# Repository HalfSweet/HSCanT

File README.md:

# HSCanT

HSCanT 是一款USB转4路CAN FD工具，基于HPM5321芯片设计。

## 特性

- 支持4路CAN FD通道
- 每路CAN FD通道支持最高8Mbit/s的数据传输速率
- 支持上位机配置可选的120Ω终端电阻
- 每路通道均支持独立的TX、RX状态全彩LED指示
- 支持最高±58V的过压保护

## 致谢

感谢[RCSN](https://github.com/RCSN)大佬提供的思路，以及该项目的上下位机软件支持。

- 上位机：<https://github.com/RCSN/cangaroo_hpmicro_canfd_analyzer>
- 下位机：<https://github.com/RCSN/hpm_sdk_extra/tree/main/demos/cangaroo_hpmicro>

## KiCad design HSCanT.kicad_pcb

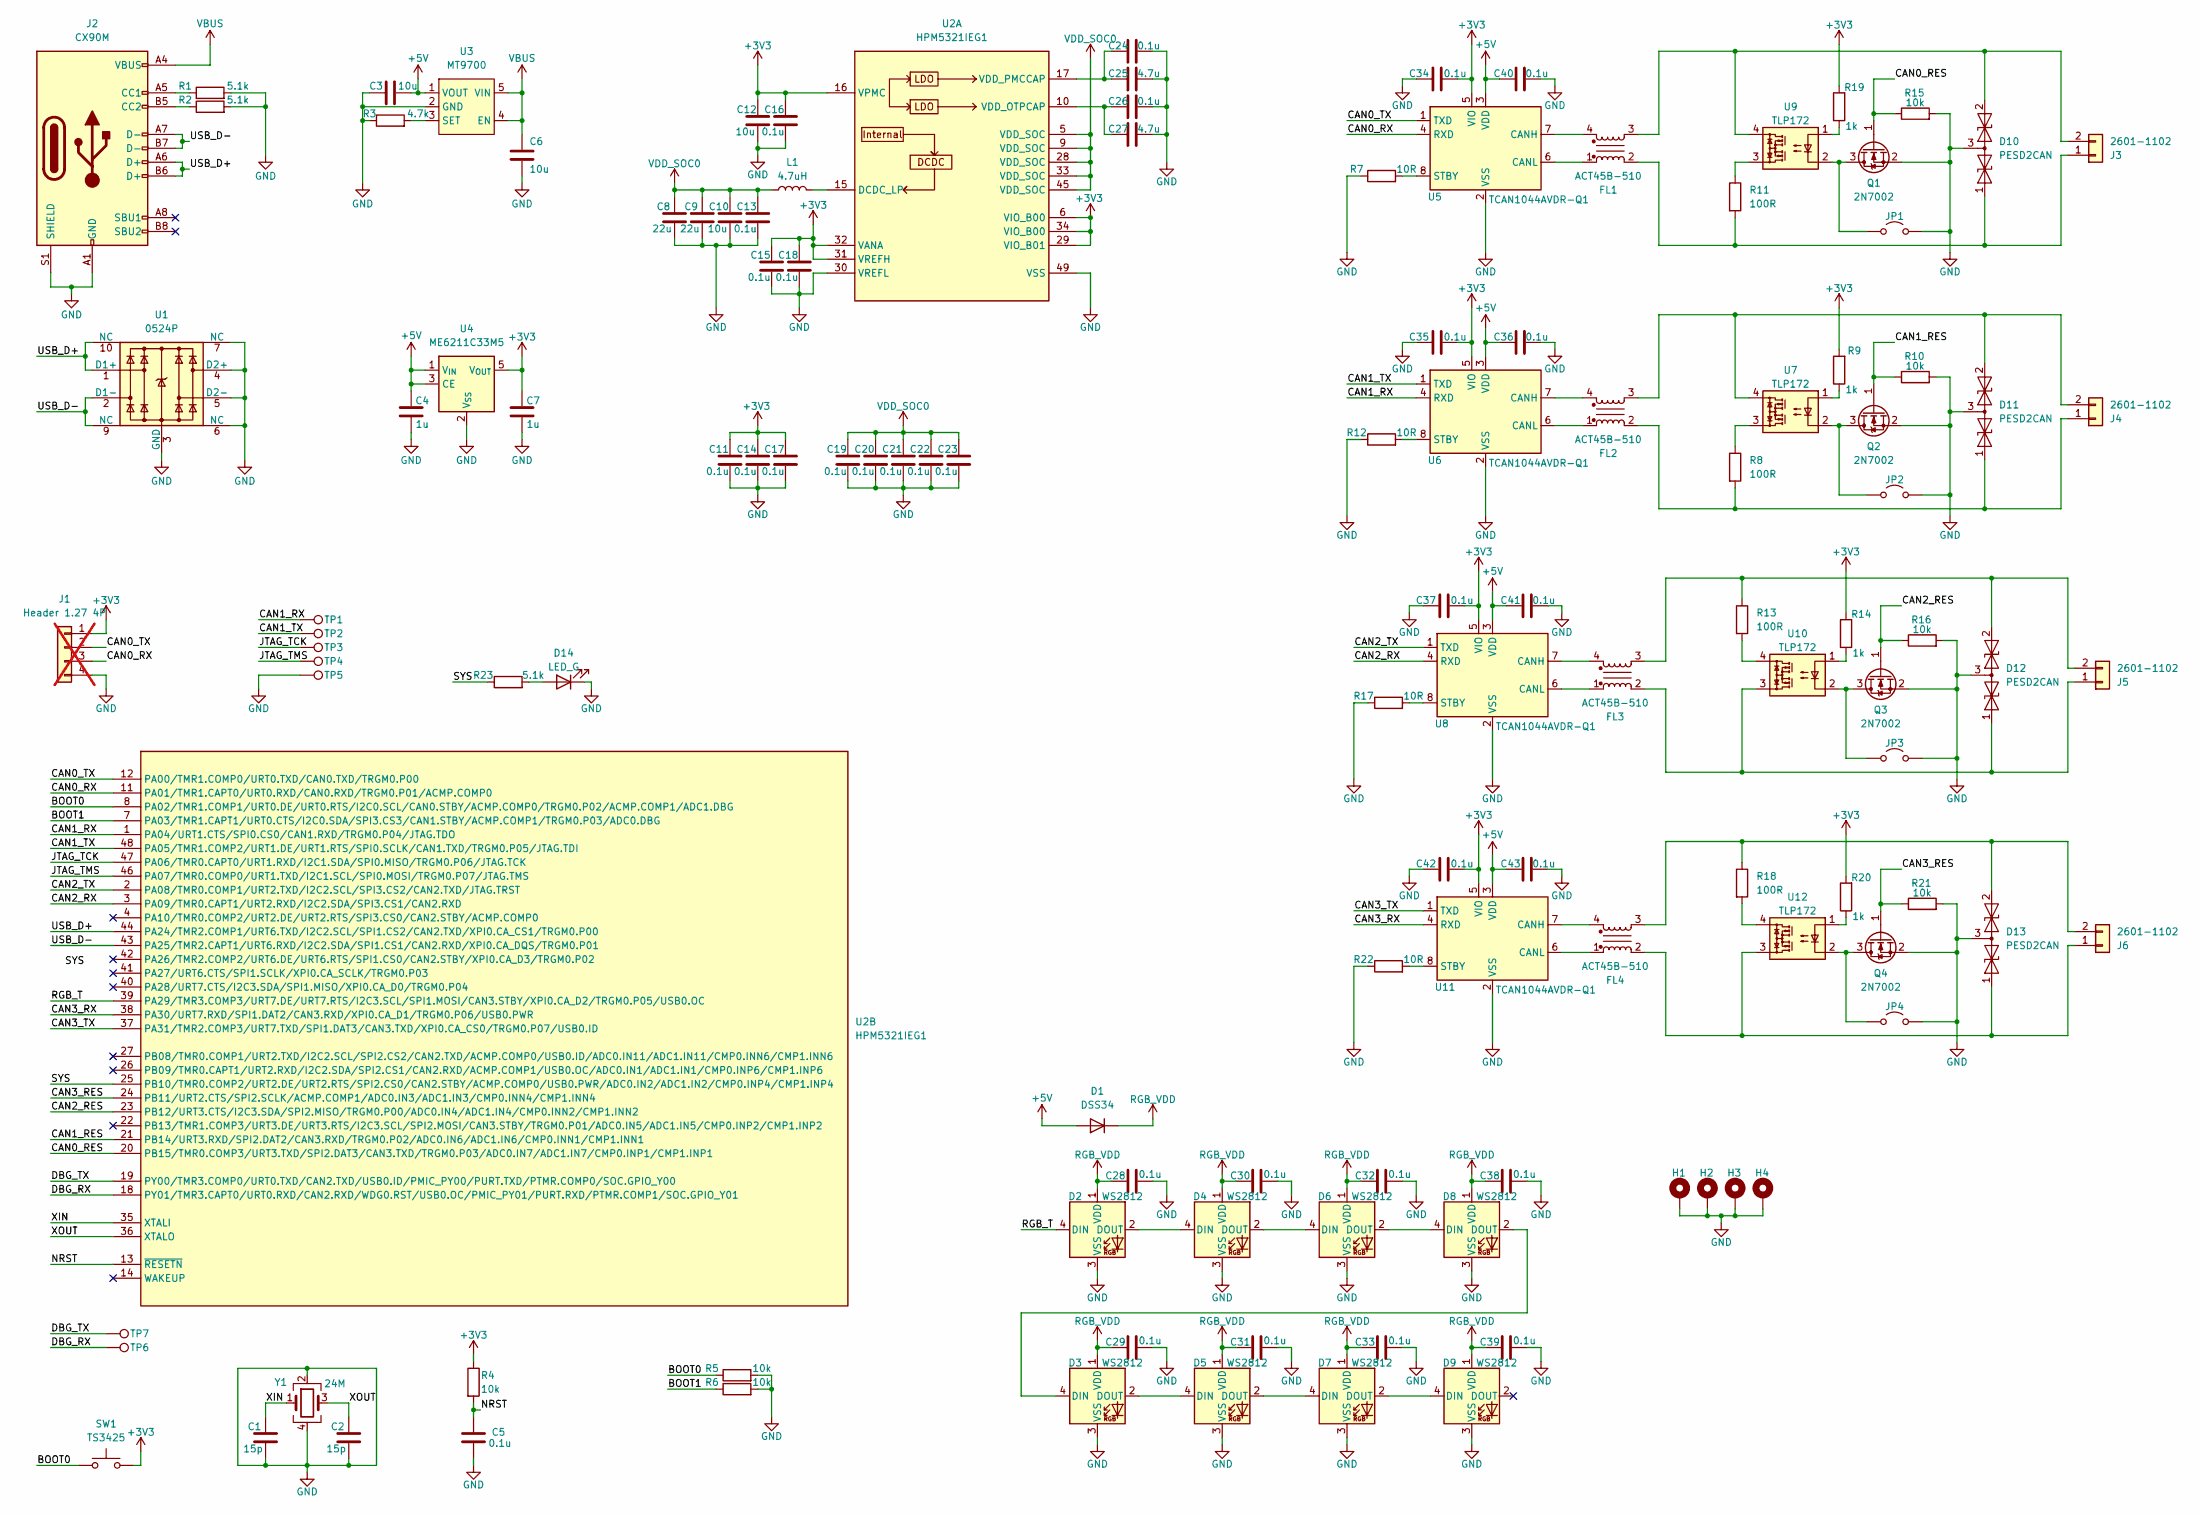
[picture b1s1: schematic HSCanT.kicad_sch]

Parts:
C1, C2: 15p; C_0402_1005Metric
C3, C6: 10u; C_0603_1608Metric
C4, C7: 1u; C_0402_1005Metric
C5, C11, C13, C14, C15, C16, C17, C18, C19, C20, C21, C22, C23, C24, C26, C28, C29, C30, C31, C32, C33, C34, C35, C36, C37, C38, C39, C40, C41, C42, C43: 0.1u; C_0402_1005Metric
C8, C9: 22u; C_0402_1005Metric
C10, C12: 10u; C_0402_1005Metric
C25, C27: 4.7u; C_0402_1005Metric
D1: DSS34; D_SOD-123
D2, D3, D4, D5, D6, D7, D8, D9: WS2812; LED_WS2812_0807
D10, D11, D12, D13: PESD2CAN; SOT-23
D14: LED_G; LED_0603_1608Metric
FL1, FL2, FL3, FL4: ACT45B-510; L_CommonModeChoke_Coilcraft_1812CAN
H1, H2, H3, H4: MountingHole_Pad; MountingHole_2.2mm_M2_Pad_TopBottom
J1: Header 1.27 4P; PinHeader_1x04_P1.27mm_Vertical; not fitted
J2: CX90M; USB-C-SMD_CX90M-16P
J3, J4, J5, J6: 2601-1102; WAGO-2601-1102
JP1, JP2, JP3, JP4: Jumper_2_Open; SolderJumper-2_P1.3mm_Open_RoundedPad1.0x1.5mm
L1: 4.7uH; L_1008_2520Metric
Q1, Q2, Q3, Q4: 2N7002; Diodes_DFN1006-3
R1, R2, R23: 5.1k; R_0402_1005Metric
R3: 4.7k; R_0402_1005Metric
R4, R5, R6, R10, R15, R16, R21: 10k; R_0402_1005Metric
R7, R12, R17, R22: 10R; R_0402_1005Metric
R8, R11, R13, R18: 100R; R_1206_3216Metric
R9, R14, R19, R20: 1k; R_0402_1005Metric
SW1: TS3425; SW_SPST_PTS810
TP1, TP2, TP3, TP4, TP5, TP6, TP7: TestPoint; TestPoint_Pad_D1.0mm
U1: 0524P; USON-10_2.5x1.0mm_P0.5mm
U2: HPM5321IEG1; QFN-48-1EP_6x6mm_P0.4mm_EP4.2x4.2mm
U3: MT9700; SOT-23-5
U4: ME6211C33M5; SOT-23-5
U5, U6, U8, U11: TCAN1044AVDR-Q1; DFN-8-1EP_3x3mm_P0.65mm_EP1.55x2.4mm
U7, U9, U10, U12: TLP172; SOP-4_3.8x4.1mm_P2.54mm
Y1: 24M; Crystal_SMD_2016-4Pin_2.0x1.6mm

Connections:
+3V3: C7.1, C11.1, C12.1, C14.1, C15.1, C16.1, C17.1, C18.1, C34.2, C35.2, C37.2, C42.2, J1.1, R4.1, R9.2, R14.2, R19.2, R20.2, SW1.2, U2.6 (VIO_B00), U2.16 (VPMC), U2.29 (VIO_B01), U2.31 (VREFH), U2.32 (VANA), U2.34 (VIO_B00), U4.5 (V_{OUT}), U5.5 (VIO), U6.5 (VIO), U8.5 (VIO), U11.5 (VIO)
+5V: C3.2, C4.1, C36.1, C40.1, C41.1, C43.1, D1.2 (A), U3.1 (VOUT), U4.1 (V_{IN}), U4.3 (CE), U5.3 (VDD), U6.3 (VDD), U8.3 (VDD), U11.3 (VDD)
/BOOT0: R5.1, SW1.1, U2.8 (PA02/TMR1.COMP1/URT0.DE/URT0.RTS/I2C0.S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)
/BOOT1: R6.1, U2.7 (PA03/TMR1.CAPT1/URT0.CTS/I2C0.SDA/SPI3.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)
/CAN0_RES: Q1.1 (G), R15.1, U2.20 (PB15/TMR0.COMP3/URT3.TXD/SPI2.DAT3/CAN3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)
/CAN0_RX: J1.3, U2.11 (PA01/TMR1.CAPT0/URT0.RXD/CAN0.RXD/TRGM0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), U5.4 (RXD)
/CAN0_TX: J1.2, U2.12 (PA00/TMR1.COMP0/URT0.TXD/CAN0.TXD/TRGM0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), U5.1 (TXD)
/CAN1_RES: Q2.1 (G), R10.1, U2.21 (PB14/URT3.RXD/SPI2.DAT2/CAN3.RXD/TRGM0.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)
/CAN1_RX: TP1.1, U2.1 (PA04/URT1.CTS/SPI0.CS0/CAN1.RXD/TRGM0.P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), U6.4 (RXD)
/CAN1_TX: TP2.1, U2.48 (PA05/TMR1.COMP2/URT1.DE/URT1.RTS/SPI0.S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), U6.1 (TXD)
/CAN2_RES: Q3.1 (G), R16.1, U2.23 (PB12/URT3.CTS/I2C3.SDA/SPI2.MISO/TRGM0.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)
/CAN2_RX: U2.3 (PA09/TMR0.CAPT1/URT2.RXD/I2C2.SDA/SPI3.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), U8.4 (RXD)
/CAN2_TX: U2.2 (PA08/TMR0.COMP1/URT2.TXD/I2C2.SCL/SPI3.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), U8.1 (TXD)
/CAN3_RES: Q4.1 (G), R21.1, U2.24 (PB11/URT2.CTS/SPI2.SCLK/ACMP.COMP1/ADC0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)
/CAN3_RX: U2.38 (PA30/URT7.RXD/SPI1.DAT2/CAN3.RXD/XPI0.C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), U11.4 (RXD)
/CAN3_TX: U2.37 (PA31/TMR2.COMP3/URT7.TXD/SPI1.DAT3/CAN3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), U11.1 (TXD)
/DBG_RX: TP6.1, U2.18 (PY01/TMR3.CAPT0/URT0.RXD/CAN2.RXD/WDG0.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)
/DBG_TX: TP7.1, U2.19 (PY00/TMR3.COMP0/URT0.TXD/CAN2.TXD/USB0.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)
/JTAG_TCK: TP3.1, U2.47 (PA06/TMR0.CAPT0/URT1.RXD/I2C1.SDA/SPI0.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)
/JTAG_TMS: TP4.1, U2.46 (PA07/TMR0.COMP0/URT1.TXD/I2C1.SCL/SPI0.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)
/NRST: C5.1, R4.2, U2.13 (~RESETN)
/RGB_T: D2.4 (DIN), U2.39 (PA29/TMR3.COMP3/URT7.DE/URT7.RTS/I2C3.S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)
/SYS: R23.1, U2.25 (PB10/TMR0.COMP2/URT2.DE/URT2.RTS/SPI2.C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)
/USB_D+: J2.A6 (D+), J2.B6 (D+), U1.1 (D1+), U1.10 (NC), U2.44 (PA24/TMR2.COMP1/URT6.TXD/I2C2.SCL/SPI1.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)
/USB_D-: J2.A7 (D-), J2.B7 (D-), U1.2 (D1-), U1.9 (NC), U2.43 (PA25/TMR2.CAPT1/URT6.RXD/I2C2.SDA/SPI1.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)
/XIN: C1.1, U2.35 (XTALI), Y1.1
/XOUT: C2.1, U2.36 (XTALO), Y1.3
GND: C1.2, C2.2, C3.1, C4.2, C5.2, C6.2, C7.2, C8.2, C9.2, C10.2, C11.2, C12.2, C13.2, C14.2, C15.2, C16.2, C17.2, C18.2, C19.2, C20.2, C21.2, C22.2, C23.2, C24.2, C25.2, C26.2, C27.2, C28.2, C29.2, C30.2, C31.2, C32.2, C33.2, C34.1, C35.1, C36.2, C37.1, C38.2, C39.2, C40.2, C41.2, C42.1, C43.2, D2.3 (VSS), D3.3 (VSS), D4.3 (VSS), D5.3 (VSS), D6.3 (VSS), D7.3 (VSS), D8.3 (VSS), D9.3 (VSS), D10.3 (common), D11.3 (common), D12.3 (common), D13.3 (common), D14.1 (K), H1.1, H2.1, H3.1, H4.1, J1.4, J2.A1 (GND), J2.A12 (GND), J2.B1 (GND), J2.B12 (GND), J2.S1 (SHIELD), JP1.2 (B), JP2.2 (B), JP3.2 (B), JP4.2 (B), Q1.2 (S), Q2.2 (S), Q3.2 (S), Q4.2 (S), R1.2, R2.2, R3.1, R5.2, R6.2, R7.1, R10.2, R12.1, R15.2, R16.2, R17.1, R21.2, R22.1, TP5.1, U1.3 (GND), U1.4 (D2+), U1.5 (D2-), U1.6 (NC), U1.7 (NC), U1.8 (GND), U2.30 (VREFL), U2.49 (VSS), U3.2 (GND), U4.2 (V_{SS}), U5.2 (VSS), U5.9 (VSS), U6.2 (VSS), U6.9 (VSS), U8.2 (VSS), U8.9 (VSS), U11.2 (VSS), U11.9 (VSS), Y1.2, Y1.4
unnamed: D2.2 (DOUT), D4.4 (DIN)
unnamed: D3.4 (DIN), D8.2 (DOUT)
unnamed: D3.2 (DOUT), D5.4 (DIN)
unnamed: D4.2 (DOUT), D6.4 (DIN)
unnamed: D5.2 (DOUT), D7.4 (DIN)
unnamed: D6.2 (DOUT), D8.4 (DIN)
unnamed: D7.2 (DOUT), D9.4 (DIN)
unnamed: D10.1 (A1), FL1.2, J3.1, R11.2
unnamed: D10.2 (A2), FL1.3, J3.2, U9.4
unnamed: D11.1 (A1), FL2.2, J4.1, R8.2
unnamed: D11.2 (A2), FL2.3, J4.2, U7.4
unnamed: D12.1 (A1), FL3.2, J5.1, U10.3
unnamed: D12.2 (A2), FL3.3, J5.2, R13.1
unnamed: D13.1 (A1), FL4.2, J6.1, U12.3
unnamed: D13.2 (A2), FL4.3, J6.2, R18.1
unnamed: D14.2 (A), R23.2
unnamed: J2.A5 (CC1), R1.1
unnamed: J2.B5 (CC2), R2.1
unnamed: JP1.1 (A), Q1.3 (D), U9.2
unnamed: JP2.1 (A), Q2.3 (D), U7.2
unnamed: JP3.1 (A), Q3.3 (D), U10.2
unnamed: JP4.1 (A), Q4.3 (D), U12.2
unnamed: R8.1, U7.3
unnamed: R9.1, U7.1
unnamed: R11.1, U9.3
unnamed: R13.2, U10.4
unnamed: R14.1, U10.1
unnamed: R18.2, U12.4
unnamed: R19.1, U9.1
unnamed: R20.1, U12.1
unnamed: L1.2, U2.15 (DCDC_LP)
unnamed: C26.1, C27.1, U2.10 (VDD_OTPCAP)
unnamed: C24.1, C25.1, U2.17 (VDD_PMCCAP)
unnamed: R3.2, U3.3 (SET)
unnamed: FL1.4, U5.7 (CANH)
unnamed: FL1.1, U5.6 (CANL)
unnamed: R7.2, U5.8 (STBY)
unnamed: FL2.4, U6.7 (CANH)
unnamed: FL2.1, U6.6 (CANL)
unnamed: R12.2, U6.8 (STBY)
unnamed: FL3.4, U8.7 (CANH)
unnamed: FL3.1, U8.6 (CANL)
unnamed: R17.2, U8.8 (STBY)
unnamed: FL4.4, U11.7 (CANH)
unnamed: FL4.1, U11.6 (CANL)
unnamed: R22.2, U11.8 (STBY)
RGB_VDD: C28.1, C29.1, C30.1, C31.1, C32.1, C33.1, C38.1, C39.1, D1.1 (K), D2.1 (VDD), D3.1 (VDD), D4.1 (VDD), D5.1 (VDD), D6.1 (VDD), D7.1 (VDD), D8.1 (VDD), D9.1 (VDD)
VBUS: C6.1, J2.A4 (VBUS), J2.A9 (VBUS), J2.B4 (VBUS), J2.B9 (VBUS), U3.4 (EN), U3.5 (VIN)
VDD_SOC0: C8.1, C9.1, C10.1, C13.1, C19.1, C20.1, C21.1, C22.1, C23.1, L1.1, U2.5 (VDD_SOC), U2.9 (VDD_SOC), U2.28 (VDD_SOC), U2.33 (VDD_SOC), U2.45 (VDD_SOC)

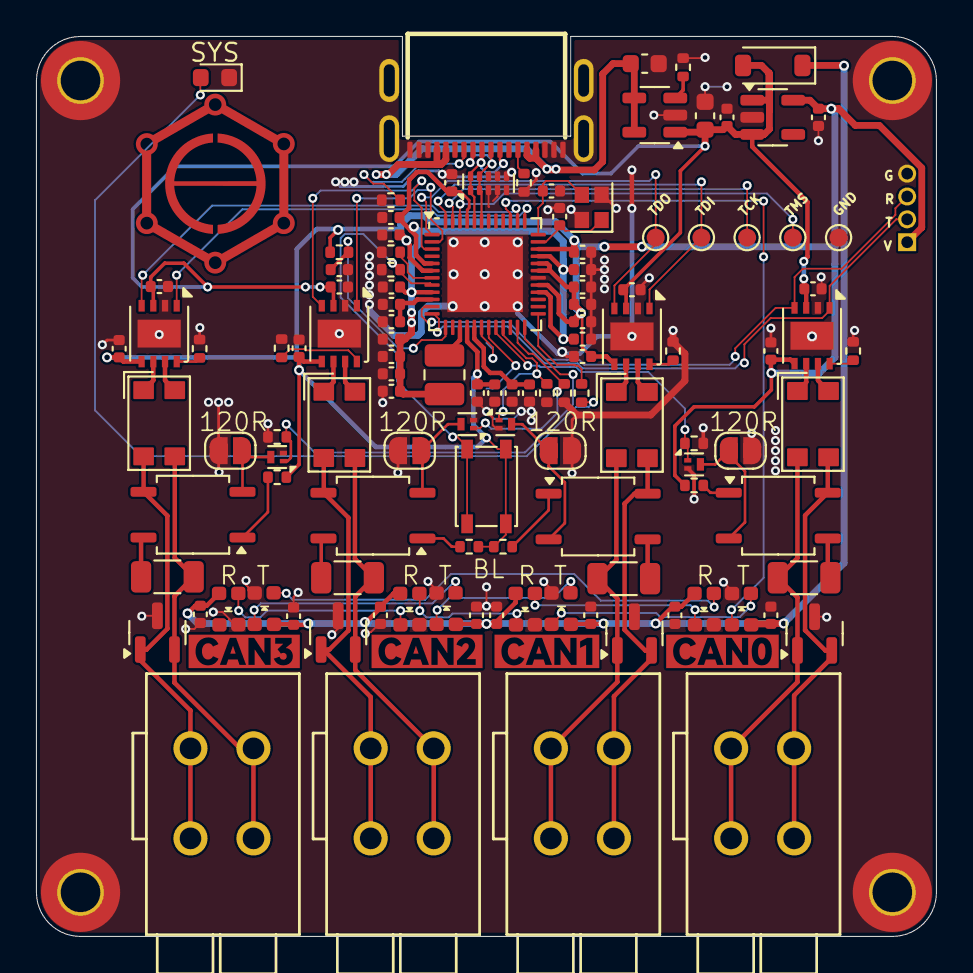
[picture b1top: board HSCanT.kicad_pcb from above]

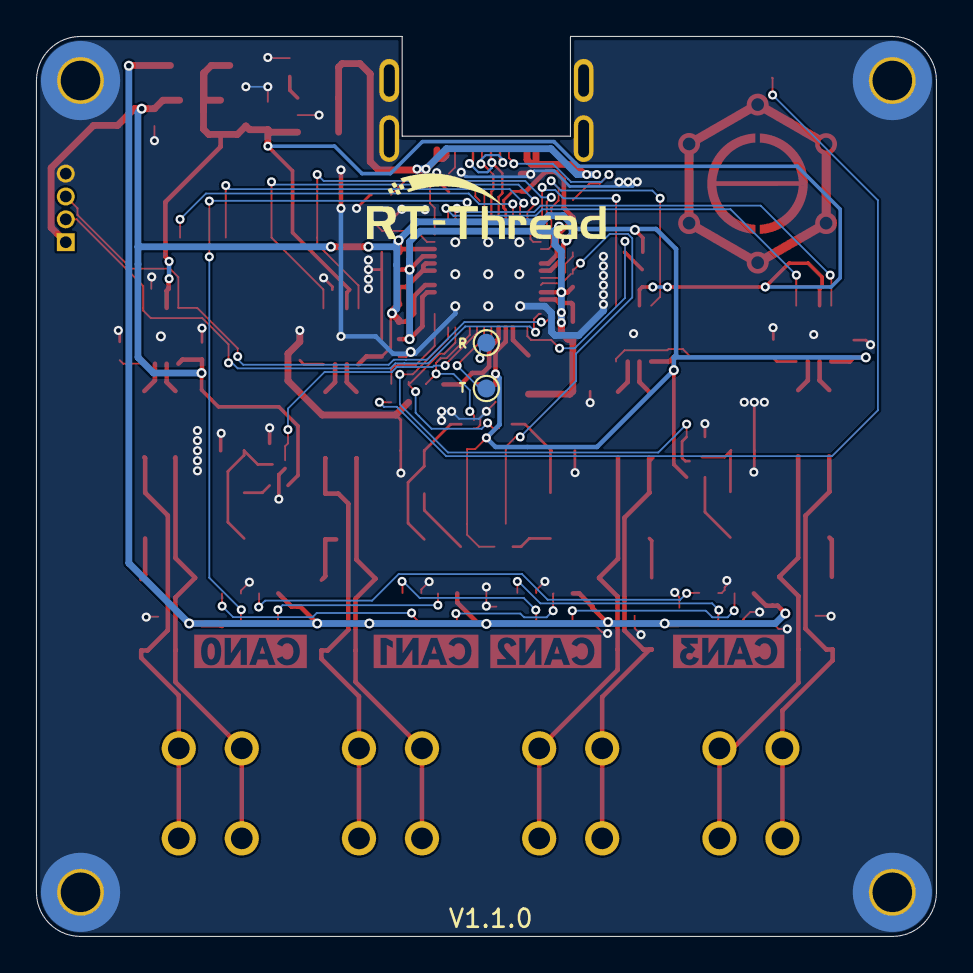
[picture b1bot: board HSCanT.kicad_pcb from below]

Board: 4 copper layers, 50.0 x 50.0 mm, 128 parts (2 on the bottom side), 77 nets.

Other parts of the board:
kibuzzard-6738A07D: G***; kibuzzard-6738A07D
kibuzzard-6738A057: G***; kibuzzard-6738A057
kibuzzard-6738A074: G***; kibuzzard-6738A074
kibuzzard-6738A091: G***; kibuzzard-6738A091

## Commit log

2024-11-19 init
2024-11-21 update: 更新原理图和PCB
2024-11-21 update: README
2024-11-21 Create LICENSE
2025-03-04 release: v1.1.0

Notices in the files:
parts and their libraries:
Copyright 2016 Accelerated Designs. All rights reserved.
